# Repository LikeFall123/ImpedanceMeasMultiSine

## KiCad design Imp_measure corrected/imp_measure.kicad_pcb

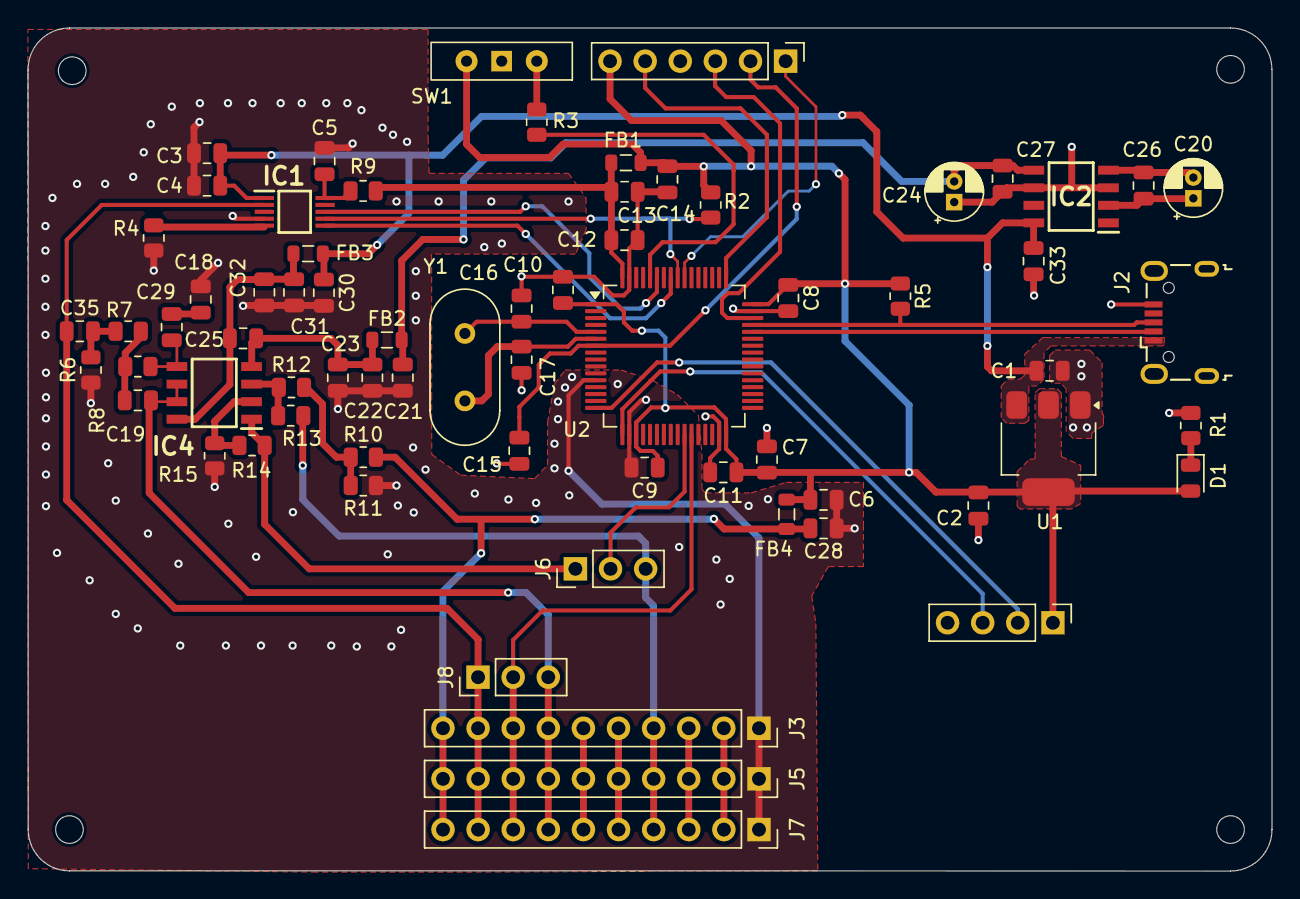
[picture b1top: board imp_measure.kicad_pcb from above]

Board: 2 copper layers, 90.0 x 61.0 mm, 73 parts (0 on the bottom side), 45 nets.

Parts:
C1, C2: 22u; C_0805_2012Metric
C3, C7, C35: 10u; C_0805_2012Metric
C4, C8, C9, C10, C11, C15, C25: 100n; C_0805_2012Metric
C5: 330n; C_0805_2012Metric
C6, C13, C14, C21, C22, C26, C27, C28, C30, C31, C33: 1u; C_0805_2012Metric
C12, C23, C32: 10n; C_0805_2012Metric
C16, C17: 10p; C_0805_2012Metric
C18, C19, C29: 1n; C_0805_2012Metric
C20, C24: 150u; CP_Radial_D4.0mm_P1.50mm
D1: LED; LED_0805_2012Metric
FB1, FB2, FB3, FB4: 120R; L_0805_2012Metric
H1, H2, H3, H4: MountingHole; MountingHole_2mm
IC1: DAC80501ZDGST; SOP50P490X110-10N
IC2: MAX660MX_NOPB; SOIC127P600X175-8N
IC4: MC33202DR2G; SOIC127P600X175-8N
J1: Conn_01x04_Pin; PinHeader_1x04_P2.54mm_Vertical
J2: USB_B_Micro; USB_Micro-B_Wuerth_629105150521
J3, J5, J7: Conn_01x10_Pin; PinSocket_1x10_P2.54mm_Vertical
J4: Conn_01x06_Pin; PinHeader_1x06_P2.54mm_Vertical
J6, J8: Conn_01x03_Pin; PinHeader_1x03_P2.54mm_Vertical
R1, R5, R9: 1k5; R_0805_2012Metric
R2, R3, R4, R6: 10k; R_0805_2012Metric
R7: 5k; R_0805_2012Metric
R8, R10, R11: 1k; R_0805_2012Metric
R12, R13, R14, R15: 10M; R_0805_2012Metric
SW1: SW_SPDT; SW_Slide-03_Wuerth-WS-SLTV_10x2.5x6.4_P2.54mm
U1: AMS1117-3.3; SOT-223-3_TabPin2
U2: STM32F401RCT6; LQFP-64_10x10mm_P0.5mm
Y1: Crystal; Crystal_HC49-U_Vertical

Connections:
+3.3V: C2.1, C6.1, C7.1, C8.1, C9.1, C10.1, C11.1, C14.1, D1.2 (A), FB1.2, FB4.2, J1.1, J4.6, R2.1, R5.1, SW1.3 (C), U1.2 (VO), U2.1 (VBAT), U2.19 (VDD), U2.32 (VDD), U2.48 (VDD)
+3.3VA: C12.1, C13.1, FB1.1, R9.1, U2.64 (VDD)
+3.3V_F: C28.1, FB4.1, J3.10, J5.10, J7.10, R10.2
/ADC1_IN4_SIGNAL: J3.4, J5.4, J6.3, J7.4, R13.2
/ADC1_IN5: J3.8, J5.8, J7.8, J8.2, U2.27 (PB1)
/ADC_IN4: J6.2, U2.26 (PB0)
/ADC_IN4_MID: IC4.1 (OUTPUT_1), J6.1, R14.1
/DAC_OUT: C35.1, IC1.2 (VOUT), J3.9, J5.9, J7.9, J8.1
/DAC_OUT_FILTERED: C19.2, IC4.6 (INPUTS_2_2), IC4.7 (OUTPUT_2), J3.7, J5.7, J7.7, J8.3
/IMP1: J3.6, J5.6, J7.6
/IMP2: J3.5, J5.5, J7.5
/IMP3: J3.2, J5.2, J7.2
/IMP4: J3.3, J5.3, J7.3
/NRST: C15.1, J4.2, U2.7 (NRST)
/PWR_LED_K: D1.1 (K), R1.1
/RCC_OSC_IN: C16.1, U2.5 (PH0), Y1.1
/RCC_OSC_OUT: C17.1, U2.6 (PH1), Y1.2
/SPI1_MOSI: IC1.8 (SDIN/SDA), U2.59 (PB7)
/SPI1_NSS: IC1.7 (~SYNC/A0), R2.2, U2.56 (PB4)
/SPI1_SCK: IC1.6 (SCLK/SCL), U2.57 (PB5)
/SYS_JTCK_SWCLK: J4.5, U2.49 (PA14)
/SYS_JTDO_SWO: J4.1, U2.55 (PB3)
/SYS_JTMS_SWDIO: J4.3, U2.46 (PA13)
/USART2_RX: J1.3, U2.17 (PA3)
/USART2_TX: J1.2, U2.16 (PA2)
/USB_OTG_FS_D+: J2.3 (D+), R5.2, U2.45 (PA12)
/USB_OTG_FS_D-: J2.2 (D-), U2.44 (PA11)
/VF_MID: R10.1, R11.2, R12.2
GND: C1.2, C2.2, C3.2, C4.2, C5.2, C6.2, C7.2, C8.2, C9.2, C10.2, C11.2, C12.2, C13.2, C14.2, C15.2, C16.2, C17.2, C18.1, C21.2, C22.2, C23.2, C24.1, C27.2, C28.2, C30.2, C31.2, C32.2, C33.1, IC1.4 (AGND), IC2.3 (GND), IC2.6 (LV), J1.4, J2.5 (GND), J3.1, J4.4, J5.1, J7.1, R1.2, R4.2, R6.1, R11.1, R15.2, SW1.1 (A), U1.1 (GND), U2.12 (VSSA), U2.18 (VSS), U2.31 (VSS), U2.47 (VSS), U2.63 (VSS)
unnamed: C18.2, C29.1
unnamed: C19.1, R7.2, R8.1
unnamed: C35.2, R6.2, R7.1
unnamed: IC1.5 (SPI2C), R4.1
unnamed: C5.1, IC1.10 (VREFIO), R9.2
unnamed: C20.1, C26.1, IC2.2 (CAP+)
unnamed: C20.2, C26.2, IC2.4 (CAP-)
unnamed: IC4.2 (INPUTS_1_1), R14.2, R15.1
unnamed: IC4.3 (INPUTS_1_2), R12.1, R13.1
unnamed: C29.2, IC4.5 (INPUTS_2_1), R8.2
unnamed: R3.1, SW1.2 (B)
unnamed: R3.2, U2.60 (BOOT0)
VBUS: C1.1, C3.1, C4.1, C30.1, C33.2, FB3.2, IC1.1 (VDD), IC2.8 (V+), J2.1 (VBUS), U1.3 (VI)
VBUS_M: C21.1, C24.2, C27.1, FB2.2, IC2.5 (OUT)
VBUS_MF: C22.1, C23.1, C25.2, FB2.1, IC4.4 (VEE)
VBUS_PF: C25.1, C31.1, C32.1, FB3.1, IC4.8 (VCC)

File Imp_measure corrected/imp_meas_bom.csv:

"Reference","Value","Datasheet","Footprint","Qty","DNP"
"C1,C2","22u","~","Capacitor_SMD:C_0805_2012Metric","2",""
"C3,C7","10u","~","Capacitor_SMD:C_0805_2012Metric","2",""
"C4,C8,C9,C10,C11,C15,C25","100n","~","Capacitor_SMD:C_0805_2012Metric","7",""
"C5","330n","~","Capacitor_SMD:C_0805_2012Metric","1",""
"C6,C13,C14,C21,C22,C26,C27,C28,C30,C31","1u","~","Capacitor_SMD:C_0805_2012Metric","10",""
"C12,C23,C32","10n","~","Capacitor_SMD:C_0805_2012Metric","3",""
"C16,C17","10p","~","Capacitor_SMD:C_0805_2012Metric","2",""
"C18,C19,C29","1n","~","Capacitor_SMD:C_0805_2012Metric","3",""
"C20,C24","150u","~","Capacitor_THT:CP_Radial_D4.0mm_P1.50mm","2",""
"D1","LED","~","LED_SMD:LED_0805_2012Metric","1",""
"FB1,FB2,FB3,FB4","120R","~","Inductor_SMD:L_0805_2012Metric","4",""
"H1,H2,H3,H4","MountingHole","~","MountingHole:MountingHole_2mm","4",""
"IC1","DAC80501ZDGST","http://www.ti.com/lit/ds/symlink/dac60501.pdf","SamacSys_Parts:SOP50P490X110-10N","1",""
"IC2","MAX660MX_NOPB","http://www.ti.com/lit/gpn/max660","SamacSys_Parts:SOIC127P600X175-8N","1",""
"IC4","MC33202DR2G","https://www.onsemi.com/pub/Collateral/MC33201-D.PDF","SamacSys_Parts:SOIC127P600X175-8N","1",""
"J1,J3,J5","Conn_01x04_Pin","~","Connector_PinHeader_2.54mm:PinHeader_1x04_P2.54mm_Vertical","3",""
"J2","USB_B_Micro","~","Connector_USB:USB_Micro-B_Wuerth_629105150521","1",""
"J4","Conn_01x06_Pin","~","Connector_PinHeader_2.54mm:PinHeader_1x06_P2.54mm_Vertical","1",""
"R1,R5","1k5","~","Resistor_SMD:R_0805_2012Metric","2",""
"R2,R3,R4","10k","~","Resistor_SMD:R_0805_2012Metric","3",""
"R6,R7","3k3","~","Resistor_SMD:R_0805_2012Metric","2",""
"R8","1k6","~","Resistor_SMD:R_0805_2012Metric","1",""
"R9","1k","~","Resistor_SMD:R_0805_2012Metric","1",""
"SW1","SW_SPDT","~","Button_Switch_THT:SW_Slide-03_Wuerth-WS-SLTV_10x2.5x6.4_P2.54mm","1",""
"U1","AMS1117-3.3","http://www.advanced-monolithic.com/pdf/ds1117.pdf","Package_TO_SOT_SMD:SOT-223-3_TabPin2","1",""
"U2","STM32F401RCT6","https://www.st.com/resource/en/datasheet/stm32f401rc.pdf","Package_QFP:LQFP-64_10x10mm_P0.5mm","1",""
"Y1","Crystal","~","Crystal:Crystal_HC49-U_Vertical","1",""

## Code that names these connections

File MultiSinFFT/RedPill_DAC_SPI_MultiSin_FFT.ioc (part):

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Mcu.Name=STM32F401R(B-C)Tx
Mcu.Package=LQFP64
Mcu.UserName=STM32F401RCTx
PA13.Mode=Serial_Wire
PA13.Signal=SYS_JTMS-SWDIO
PA14.Mode=Serial_Wire
PA14.Signal=SYS_JTCK-SWCLK
PA15.GPIOParameters=GPIO_PuPd
PA15.GPIO_PuPd=GPIO_NOPULL
PA15.Signal=GPIO_Input
PA2.Mode=Asynchronous
PA2.Signal=USART2_TX
PA3.Mode=Asynchronous
PA3.Signal=USART2_RX
PA4.Signal=GPIO_Input
PA5.Mode=Simplex_Bidirectional_Master
PA5.Signal=SPI1_SCK
PA6.Signal=GPIO_Input
PA7.Mode=Simplex_Bidirectional_Master
PA7.Signal=SPI1_MOSI
PB0.Signal=ADCx_IN8
PB1.Signal=ADCx_IN9
PB10.Signal=GPIO_Input
PB2.Signal=GPIO_Input
PB4.GPIOParameters=GPIO_Speed,GPIO_Label
PB4.GPIO_Label=SPI_SW_NSS
PB4.GPIO_Speed=GPIO_SPEED_FREQ_LOW
PB4.Signal=GPIO_Output
PB5.Signal=GPIO_Input
PC10.GPIOParameters=GPIO_PuPd
PC10.GPIO_PuPd=GPIO_NOPULL
PC10.Signal=GPIO_Input
PC11.Signal=GPIO_Input
PC12.Signal=GPIO_Input
PC4.Signal=GPIO_Input
PC5.Signal=GPIO_Input
PH0\ -\ OSC_IN.Mode=HSE-External-Oscillator
PH0\ -\ OSC_IN.Signal=RCC_OSC_IN
PH1\ -\ OSC_OUT.Mode=HSE-External-Oscillator
PH1\ -\ OSC_OUT.Signal=RCC_OSC_OUT
RCC.HSE_VALUE=16000000
RCC.SYSCLKFreq_VALUE=51200000
RCC.SYSCLKSource=RCC_SYSCLKSOURCE_PLLCLK
board=custom

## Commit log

2024-12-18 KiCad project
    The designed hardware in KiCad. It is the corrected version:
    -SPI connection
    -Vcap and Vref+
    -Sallen-Key without highpass
    (SPDT should be corrected)
2024-12-18 Multisine measurement C project
    EWARM project C code with STMCubeMX configurations. Measuring impedance with multisine excitation using a DAC80501 and a STM32F401 MCU.
2024-12-18 Impedance measurement with 5 param LSM.
    EWARM project C code with STMCubeMX configurations. Measuring impedance with multisine excitation using a DAC80501 and a STM32F401 MCU. The excitation contains 2 sines, and the MCU uses the 5 paramet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
2024-12-18 MATLAB files
    MATLAB files for signal generation and post processing of the MCU data sent on serial port.
    Measurement data series of the impedance.
2024-12-18 Impedance measurement data
    Data measured with different impedance models and sampling it with different frequencies.
